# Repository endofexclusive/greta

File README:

The GRETA expansion board for the Amiga 500 computer has SDRAM,
microSD mass storage and Ethernet controllers. It is built on
FPGA technology.

The intended audience is any person who wants to learn more
about how to develop hardware for the Amiga computer in general,
and especially the one who wants to develop the GRETA expansion
further.

All schematics, PCB layout and VHDL code described in this
document are released under the GNU General Public License,
version 3. Gerber files are readily available and can be sent
to a PCB manufacturer for production. Refer to the schematic
files for bill of materials (BOM).

As of January 2014, some features are still to be implemented
in VHDL, namely microSD controller and Ethernet MAC,  as well
as corresponding software device drivers on the Amiga.

For a description of the design, se the file doc/greta.pdf.

The original author is Martin Åberg. He can be contacted on
electronic mail (remove spaces):

m ar t in AT f ri p os t DOT o rg

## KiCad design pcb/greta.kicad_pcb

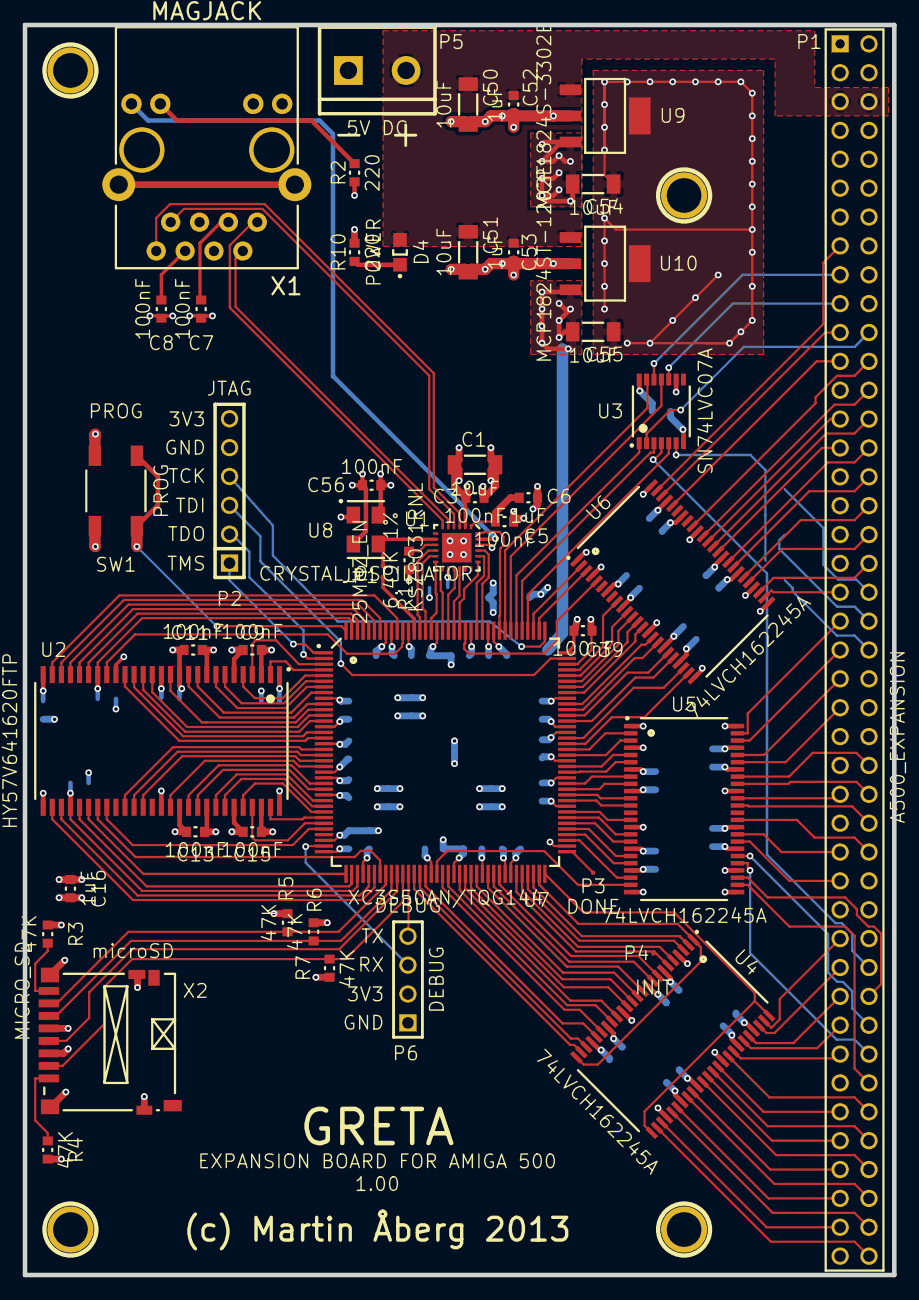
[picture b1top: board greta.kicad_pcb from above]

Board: 4 copper layers, 76.5 x 110.0 mm, 94 parts (0 on the bottom side), 184 nets.

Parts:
C1, C2, C50, C51, C54, C55: 10uF; CAP3216
C3, C4, C5, C7, C8, C9, C10, C11, C12, C13, C14, C15, C17, C18, C19, C20, C21, C22, C23, C24, C25, C26, C27, C28, C29, C30, C31, C32, C33, C34, C35, C36, C37, C38, C39, C40, C41, C42, C43, C44, C45, C56: 100nF; CAP1608
C6, C16, C46, C47, C48, C49, C52, C53: 1uF; CAP1608
D1, D2, D3: B0520WS; SOD-323
D4: POWER; LED2012
JP1: 25MHZ_EN; JUMPER2
NE: P***; 1pin
NW: P***; 1pin
P1: A500_EXPANSION
P2: JTAG; PIN_ARRAY-6X1
P3: DONE; TESTPOINT
P4: INIT; TESTPOINT
P5: 5V DC; bornier2
P6: DEBUG; PIN_ARRAY_4x1
R1: 6.49K 1%; RES1608
R2, R10: 220; RES1608
R3, R4, R5, R6, R7: 47K; RES1608
R8, R9: 1K; RES1608
SE: P***; 1pin
SW: P***; 1pin
SW1: PROG; BUTTON52x52
U1: KSZ8031RNL; QFN44-24
U2: HY57V641620FTP; TSOP2-54
U3: SN74LVC07A; TSSOP14
U4, U5, U6: 74LVCH162245A; SSOP48
U7: XC3S50AN/TQG144; TQ144
U8: CRYSTAL_OSCILLATOR; OSC50x32
U9: MCP1824S-3302E; SOT-223
U10: MCP1824ST-1202E; SOT-223
X1: MAGJACK
X2: MICRO_SD

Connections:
25MHZ: JP1.1, U1.8, U8.3
+1.2V: C30.1, C34.1, C38.1, C42.1, C46.1, C55.1, U7.22, U7.52, U7.94, U7.122, U10.3
+3.3V: C1.1, C2.1, C3.1, C4.1, C9.1, C10.1, C11.1, C12.1, C13.1, C14.1, C15.1, C16.1, C17.1, C18.1, C19.1, C20.1, C21.1, C22.1, C23.1, C24.1, C25.1, C26.1, C27.1, C28.1, C29.1, C31.1, C32.1, C33.1, C35.1, C36.1, C37.1, C39.1, C40.1, C41.1, C43.1, C44.1, C45.1, C47.1, C48.1, C49.1, C54.1, C56.1, P2.6, P6.2, R2.1, R3.1, R4.1, R5.1, R6.1, R7.1, U1.2, U1.14, U2.1, U2.3, U2.9, U2.14, U2.27, U2.43, U2.49, U3.14, U4.7, U4.18, U4.31, U4.42, U5.1, U5.7, U5.18, U5.24, U5.31, U5.42, U6.1, U6.7, U6.18, U6.24, U6.31, U6.42, U7.14, U7.23, U7.36, U7.40, U7.61, U7.66, U7.86, U7.95, U7.108, U7.119, U7.133, U7.136, U8.1, U8.4, U9.3, X2.4
+5V: C50.1, C51.1, C52.1, C53.1, D4.1, P1.5, P1.6, P5.2, U9.1, U10.1
/FPGA/DONE: P3.1, U7.73
/FPGA/PROG_B: SW1.3, SW1.4, U7.144
/FPGA/RX: P6.3, U7.35
/FPGA/TCK: P2.4, U7.109
/FPGA/TDI: P2.3, U7.107
/FPGA/TDO: P2.2, U7.2
/FPGA/TMS: P2.1, U7.1
/FPGA/TX: P6.4, U7.48
/Rock Lobster/RL_A1: P1.29, U6.35
/Rock Lobster/RL_A2: P1.27, U6.37
/Rock Lobster/RL_A3: P1.26, U6.38
/Rock Lobster/RL_A4: P1.24, U6.40
/Rock Lobster/RL_A5: P1.21, U6.46
/Rock Lobster/RL_A6: P1.23, U6.44
/Rock Lobster/RL_A7: P1.28, U6.36
/Rock Lobster/RL_A8: P1.30, U6.33
/Rock Lobster/RL_A9: P1.32, U6.32
/Rock Lobster/RL_A10: P1.34, U6.30
/Rock Lobster/RL_A11: P1.36, U6.29
/Rock Lobster/RL_A12: P1.38, U6.27
/Rock Lobster/RL_A13: P1.39, U6.26
/Rock Lobster/RL_A14: P1.41, U5.47
/Rock Lobster/RL_A15: P1.43, U5.46
/Rock Lobster/RL_A16: P1.45, U5.44
/Rock Lobster/RL_A17: P1.47, U5.43
/Rock Lobster/RL_A18: P1.52, U5.41
/Rock Lobster/RL_A19: P1.54, U5.40
/Rock Lobster/RL_A20: P1.56, U5.37
/Rock Lobster/RL_A21: P1.58, U5.35
/Rock Lobster/RL_A22: P1.57, U5.33
/Rock Lobster/RL_A23: P1.59, U5.32
/Rock Lobster/RL_CDAC: P1.15, U6.47
/Rock Lobster/RL_D0: P1.75, U4.38
/Rock Lobster/RL_D1: P1.77, U4.36
/Rock Lobster/RL_D2: P1.79, U4.33
/Rock Lobster/RL_D3: P1.81, U4.30
/Rock Lobster/RL_D4: P1.83, U4.27
/Rock Lobster/RL_D5: P1.86, U4.26
/Rock Lobster/RL_D6: P1.84, U4.29
/Rock Lobster/RL_D7: P1.82, U4.32
/Rock Lobster/RL_D8: P1.80, U4.35
/Rock Lobster/RL_D9: P1.78, U4.37
/Rock Lobster/RL_D10: P1.76, U4.40
/Rock Lobster/RL_D11: P1.71, U4.41
/Rock Lobster/RL_D12: P1.69, U4.43
/Rock Lobster/RL_D13: P1.67, U4.44
/Rock Lobster/RL_D14: P1.65, U4.46
/Rock Lobster/RL_D15: P1.63, U4.47
/Rock Lobster/RL_RnW: P1.68, U5.27
/Rock Lobster/RL_nAS: P1.74, U5.26
/Rock Lobster/RL_nDTACK: P1.66, U3.4
/Rock Lobster/RL_nINT2: P1.19, U3.10
/Rock Lobster/RL_nINT6: P1.22, U3.2
/Rock Lobster/RL_nINT7: D1.2, D2.2, D3.2, U3.6
/Rock Lobster/RL_nLDS: P1.70, U5.30
/Rock Lobster/RL_nOVR: P1.17, U3.12
/Rock Lobster/RL_nRST: P1.53, U5.38
/Rock Lobster/RL_nUDS: P1.72, U5.29
A1: U6.14, U7.101
A2: U6.12, U7.103
A3: U6.11, U7.104
A4: U6.9, U7.105
A5: U6.3, U7.110
A6: U6.5, U7.123
A7: U6.13, U7.102
A8: U6.16, U7.99
A9: U6.17, U7.98
A10: U6.19, U7.97
A11: U6.20, U7.96
A12: U6.22, U7.93
A13: U6.23, U7.92
A14: U5.2, U7.91
A15: U5.3, U7.90
A16: U5.5, U7.88
A17: U5.6, U7.87
A18: U5.8, U7.85
A19: U5.9, U7.84
A20: U5.12, U7.82
A21: U5.14, U7.80
A22: U5.16, U7.79
A23: U5.17, U7.78
CDAC: U6.2, U7.111
CKE: U2.37, U7.18
CLK: U2.38, U7.19
D0: U4.11, U7.62
D1: U4.13, U7.59
D2: U4.16, U7.57
D3: U4.19, U7.54
D4: U4.22, U7.50
D5: U4.23, U7.49
D6: U4.20, U7.51
D7: U4.17, U7.55
D8: U4.14, U7.58
D9: U4.12, U7.60
D10: U4.9, U7.63
D11: U4.8, U7.64
D12: P4.1, U4.6, U7.67
D13: U4.5, U7.68
D14: U4.3, U7.69
D15: U4.2, U7.70
DQ0: U2.2, U7.4
DQ1: U2.4, U7.3
DQ2: U2.5, U7.5
DQ3: U2.7, U7.6
DQ4: U2.8, U7.7
DQ5: U2.10, U7.8
DQ6: U2.11, U7.10
DQ7: U2.13, U7.11
DQ8: U2.42, U7.21
DQ9: U2.44, U7.24
DQ10: U2.45, U7.25
DQ11: U2.47, U7.27
DQ12: U2.48, U7.28
DQ13: U2.50, U7.29
DQ14: U2.51, U7.31
DQ15: U2.53, U7.30
GND: C1.2, C2.2, C3.2, C4.2, C5.2, C6.2, C7.2, C8.2, C9.2, C10.2, C11.2, C12.2, C13.2, C14.2, C15.2, C16.2, C17.2, C18.2, C19.2, C20.2, C21.2, C22.2, C23.2, C24.2, C25.2, C26.2, C27.2, C28.2, C29.2, C30.2, C31.2, C32.2, C33.2, C34.2, C35.2, C36.2, C37.2, C38.2, C39.2, C40.2, C41.2, C42.2, C43.2, C44.2, C45.2, C46.2, C47.2, C48.2, C49.2, C50.2, C51.2, C52.2, C53.2, C54.2, C55.2, C56.2, P1.1, P1.2, P1.3, P1.4, P1.12, P1.13, P1.25, P1.37, P1.49, P1.61, P1.73, P1.85, P2.5, P5.1, P6.1, R1.2, R8.1, R9.2, R10.2, SW1.1, SW1.2, U1.22, U1.25, U2.6, U2.12, U2.19, U2.28, U2.41, U2.46, U2.52, U2.54, U3.7, U3.9, U4.4, U4.10, U4.15, U4.21, U4.28, U4.34, U4.39, U4.45, U5.4, U5.10, U5.15, U5.21, U5.25, U5.28, U5.34, U5.39, U5.45, U5.48, U6.4, U6.10, U6.15, U6.21, U6.25, U6.28, U6.34, U6.39, U6.45, U6.48, U7.9, U7.17, U7.26, U7.34, U7.56, U7.65, U7.74, U7.81, U7.89, U7.100, U7.106, U7.118, U7.128, U7.137, U8.2, U9.2, U9.4, U10.2, U10.4, X2.6, X2.9, X2.10, X2.12, X2.13
GNDPWR: X1.13, X1.14
LDQM: U2.15, U7.12
MDC: U1.11, U7.130
MDIO: U1.10, U7.131
unnamed: D4.2, R10.1
unnamed: JP1.2, U7.132
unnamed: D1.1, P1.40
unnamed: D2.1, P1.42
unnamed: D3.1, P1.44
unnamed: R3.2, X2.1
unnamed: R4.2, X2.8
unnamed: U1.3, X1.8
unnamed: U1.5, X1.2
unnamed: C7.1, X1.3
unnamed: U1.23, X1.12
unnamed: C8.1, X1.6
unnamed: R2.2, X1.11
unnamed: U1.6, X1.1
unnamed: U1.4, X1.7
unnamed: R1.1, U1.9
unnamed: C5.1, C6.1, U1.1
PHY_nRST: U1.24, U7.117
RL_TO_GRETA: U4.1, U4.24, U7.71
RL_nOE: U4.25, U4.48, U7.72
RMII_CRS_DV: U1.15, U7.126
RMII_REF_CLK: U1.16, U7.125
RMII_RXD0: U1.13, U7.127
RMII_RXD1: U1.12, U7.129
RMII_TXD0: U1.20, U7.121
RMII_TXD1: U1.21, U7.120
RMII_TX_EN: U1.19, U7.124
RnW: U5.22, U7.75
SDRAM_A0: U2.23, U7.141
SDRAM_A1: U2.24, U7.139
SDRAM_A2: U2.25, U7.138
SDRAM_A3: U2.26, U7.135
SDRAM_A4: U2.29, U7.42
SDRAM_A5: U2.30, U7.41
SDRAM_A6: R9.1, U2.31, U7.39
SDRAM_A7: U2.32, U7.38
SDRAM_A8: U2.33, U7.37
SDRAM_A9: U2.34, U7.43
SDRAM_A10: U2.22, U7.142
SDRAM_A11: U2.35, U7.32
SDRAM_BA0: U2.20, U7.134
SDRAM_BA1: R8.2, U2.21, U7.143
SD_CLK: U7.46, X2.5
SD_DI: R6.2, U7.45, X2.3
SD_DO: R7.2, U7.47, X2.7
SD_nCS: R5.2, U7.44, X2.2
UDQM: U2.39, U7.20
nAS: U5.23, U7.53
nCAS: U2.17, U7.15
nDTACK: U3.3, U7.113
nINT2: U3.11, U7.115
nINT6: U3.1, U7.114
nINT7: U3.5, U7.112
nLDS: U5.19, U7.77
nOVR: U3.13, U7.116
nRAS: U2.18, U7.16
nRST: U5.11, U7.83
nUDS: U5.20, U7.76
nWE: U2.16, U7.13

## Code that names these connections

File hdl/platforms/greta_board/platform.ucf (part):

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NET "PHY_MDIO" LOC = P131;
NET "PHY_MDIO" PULLUP;
NET "PHY_nRST" IOSTANDARD = LVCMOS33;
NET "PHY_nRST" LOC = P117;
NET "RL_A[10]" IOSTANDARD = LVCMOS33;
NET "RL_A[10]" LOC = P97;
NET "RL_A[11]" IOSTANDARD = LVCMOS33;
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NET "RL_A[9]" IOSTANDARD = LVCMOS33;
NET "RL_A[9]" LOC = P98;
NET "RL_CDAC" IOSTANDARD = LVCMOS33;
NET "RL_CDAC" LOC = P111;
NET "RL_D[0]" IOSTANDARD = LVCMOS33;
NET "RL_D[0]" LOC = P62;
NET "RL_D[10]" IOSTANDARD = LVCMOS33;
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NET "RL_D_TO_GRETA" IOSTANDARD = LVCMOS33;
NET "RL_D_TO_GRETA" LOC = P71;
NET "RL_nAS" IOSTANDARD = LVCMOS33;
NET "RL_nAS" LOC = P53;
NET "RL_nDTACK" IOSTANDARD = LVCMOS33;
NET "RL_nDTACK" LOC = P113;
NET "RL_nINT2" IOSTANDARD = LVCMOS33;
NET "RL_nINT2" LOC = P115;
NET "RL_nINT6" IOSTANDARD = LVCMOS33;
NET "RL_nINT6" LOC = P114;
NET "RL_nINT7" IOSTANDARD = LVCMOS33;
NET "RL_nINT7" LOC = P112;
NET "RL_nLDS" IOSTANDARD = LVCMOS33;
NET "RL_nLDS" LOC = P77;
NET "RL_nOVR" IOSTANDARD = LVCMOS33;
NET "RL_nOVR" LOC = P116;
NET "RL_nRST" IOSTANDARD = LVCMOS33;
NET "RL_nRST" LOC = P83;
NET "RL_nUDS" IOSTANDARD = LVCMOS33;
NET "RL_nUDS" LOC = P76;
NET "RL_RnW" IOSTANDARD = LVCMOS33;
NET "RL_RnW" LOC = P75;
NET "RMII_CRS_DV" IOSTANDARD = LVCMOS33;
NET "RMII_CRS_DV" LOC = P126;
NET "RMII_REF_CLK" IOSTANDARD = LVCMOS33;
NET "RMII_REF_CLK" LOC = P125;
NET "RMII_RXD[0]" IOSTANDARD = LVCMOS33;
NET "RMII_RXD[0]" LOC = P127;
NET "RMII_RXD[1]" IOSTANDARD = LVCMOS33;
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NET "RMII_TXD[1]" IOSTANDARD = LVCMOS33;
NET "RMII_TXD[1]" LOC = P120;
NET "RMII_TX_EN" IOSTANDARD = LVCMOS33;
NET "RMII_TX_EN" LOC = P124;
NET "SDRAM_A[0]" IOSTANDARD = LVCMOS33;
NET "SDRAM_A[0]" LOC = P141;
NET "SDRAM_A[10]" IOSTANDARD = LVCMOS33;
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# Hynix SDRAM:
# Access Time From Clock, CL=3: tAC3 max 5.4 ns
# Data-out Hold Time: tOH min 2.5 ns
#OFFSET = OUT AFTER RMII_REF_CLK REFERENCE_PIN SDRAM_CLK;

INST "SDRAM_DQ<0>" TNM = SDRAM_IN;
INST "SDRAM_DQ<1>" TNM = SDRAM_IN;
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
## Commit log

2014-01-06 First public release.
2014-04-01 Removed references to Rock lobster (A500 motherboard).
2016-07-30 Include Makefile for simulation
2016-07-30 Bus functional model for GRETA bus protocol
2016-07-31 Common GRETA bus in signal
    A common gbus_in signal record can be input to all slaves. config_in is
    represented as a vector of all slaves. Added interrupt output.
2016-07-31 Scripts for VHDL and C user register info.
    A single YAML representation is used to generate VHDL user register
    encoding/decoding and C header files describing the user registers.
2016-07-31 HDL .gitignore
    We do not care about GHDL and synthesis files.
2016-07-31 GRETA SPI controller
    - The controller performs one transaction at a time.
    - Level interrupt (maskable) is generated when transfer completes.
    - Optional slave select output with configurable polarity.
    - SPI clock frequency is programmable.
    - Register description is provided in aspic_regs.{yaml,vhdl,h}
2016-07-31 HDL design with SPI controller
2019-10-12 ASPIC: No automatic slave select
    The device driver is responsible for asserting SPI select.
2019-10-12 HDL: SPI_DI is mosi, SPI_DO is miso
2019-10-12 README: rewritten
2019-10-12 DOC: added errata

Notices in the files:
hdl/platforms/greta_board/platform.ucf:
Copyright (C) 2013 Martin Åberg
Public License along with this program.  If not, see
<http://www.gnu.org/licenses/>.
pcb/greta.kicad_pcb:
This schematic is licensed under the terms of GNU GPL version 3.
